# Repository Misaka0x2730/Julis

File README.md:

# Julis
Expansion test board of ARM Debugger for NUCLEO-F746ZG.

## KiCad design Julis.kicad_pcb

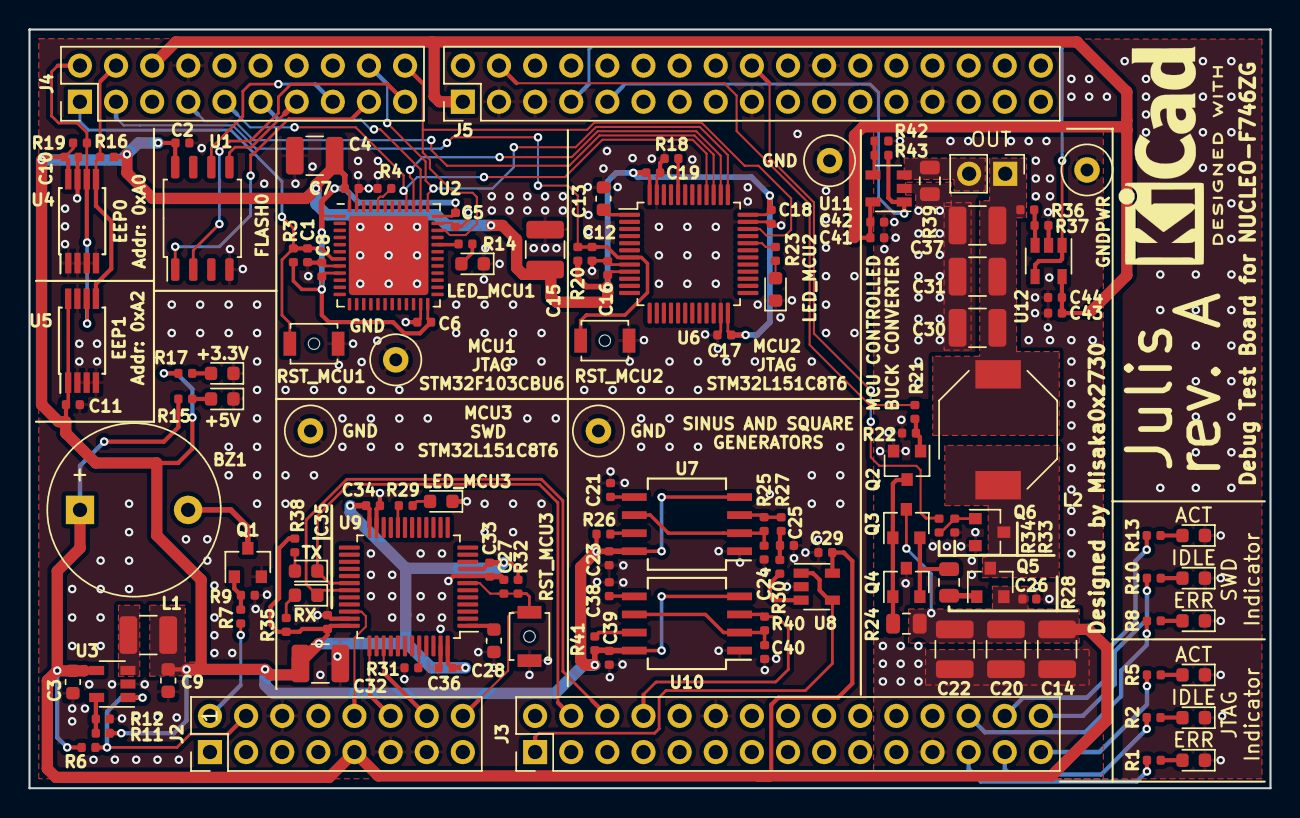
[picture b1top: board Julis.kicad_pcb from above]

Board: 2 copper layers, 87.2 x 53.3 mm, 134 parts (0 on the bottom side), 83 nets.

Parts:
BZ1: HCM1205X; Buzzer_12x9.5RM7.6
C1, C2, C5, C6, C7, C8, C10, C11, C12, C16, C17, C18, C19, C21, C23, C26, C27, C29, C33, C34, C35, C36, C38, C39, C41, C43: 0.1uF; C_0402_1005Metric
C3: 4.7uF; C_0603_1608Metric
C4, C14, C15, C20, C22, C30, C31, C32, C37: 22uF; C_1210_3225Metric
C9: 10uF; C_0603_1608Metric
C13, C28: 1uF; C_0603_1608Metric
C24, C25, C40: 68pF; C_0402_1005Metric
C42, C44: 10nF; C_0402_1005Metric
D1, D4: ERR; LED_0603_1608Metric
D2, D5: IDLE; LED_0603_1608Metric
D3, D6: ACT; LED_0603_1608Metric
D7: LED_MCU1; LED_0603_1608Metric
D8: +5V; LED_0603_1608Metric
D9: +3.3V; LED_0603_1608Metric
D10: LED_MCU2; LED_0603_1608Metric
D11: LED_MCU3; LED_0603_1608Metric
D12: RX; LED_0603_1608Metric
D13: TX; LED_0603_1608Metric
J1: OUT; PinHeader_1x02_P2.54mm_Vertical
J2: Conn_02x08_Odd_Even; PinHeader_2x08_P2.54mm_Vertical
J3: Conn_02x15_Odd_Even; PinHeader_2x15_P2.54mm_Vertical
J4: Conn_02x10_Odd_Even; PinHeader_2x10_P2.54mm_Vertical
J5: Conn_02x17_Odd_Even; PinHeader_2x17_P2.54mm_Vertical
L1: 2.2uH; L_1210_3225Metric
L2: 100uH; L_Bourns-SRU8043
Q1, Q2, Q6: IRLML2502; SOT-23
Q3: BC817; SOT-23
Q4: BC807; SOT-23
Q5: IRLML6402; SOT-23
R1, R2, R5, R8, R10, R13, R14, R15, R17, R23, R29, R35, R38: 510; R_0402_1005Metric
R3, R4, R18, R20, R31, R32: 10k; R_0402_1005Metric
R6, R9, R12, R22, R25, R26, R33, R36, R37, R40, R41: 100k; R_0402_1005Metric
R7, R21, R30, R34, R42: 1k; R_0402_1005Metric
R11: 453k; R_0402_1005Metric
R16, R19: 3.3k; R_0402_1005Metric
R24: 1k; R_0805_2012Metric
R27: 24k; R_0402_1005Metric
R28: 33; R_0805_2012Metric
R39: 0.1; R_0805_2012Metric
R43: 200k; R_0402_1005Metric
SW1: RST_MCU1; SW_SPST_B3U-1000P-B
SW2: RST_MCU2; SW_SPST_B3U-1000P-B
SW3: RST_MCU3; SW_SPST_B3U-1000P-B
TP1: GNDPWR; TestPoint_Loop_D3.50mm_Drill0.9mm_Beaded
TP2, TP3, TP4, TP5: GND; TestPoint_Loop_D3.50mm_Drill0.9mm_Beaded
U1: W25Q32JVSS; SOIC-8_5.23x5.23mm_P1.27mm
U2: STM32F103CBUx; QFN-48-1EP_7x7mm_P0.5mm_EP5.6x5.6mm
U3: TLV62568DBV; SOT-23-5
U4, U5: M24C02-WDW; TSSOP-8_4.4x3mm_P0.65mm
U6, U9: STM32L151C8TxA; LQFP-48_7x7mm_P0.5mm
U7, U10: LMC555xM; SO-8_5.3x6.2mm_P1.27mm
U8, U11, U12: TLV2371DBV; SOT-23-5

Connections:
+3V3: C2.2, C4.2, C5.2, C6.2, C7.2, C8.2, C9.1, C10.2, C11.2, C15.2, C16.2, C17.2, C18.2, C19.2, C23.2, C32.2, C33.2, C34.2, C35.2, C36.2, C39.2, L1.2, R3.1, R11.2, R16.1, R17.1, R19.1, R20.1, R26.2, R32.1, R35.1, R38.1, R41.2, U1.8, U2.1, U2.9, U2.24, U2.36, U2.48, U4.8, U5.1, U5.8, U6.9, U6.24, U6.36, U6.48, U7.4, U7.8, U9.9, U9.24, U9.36, U9.48, U10.4, U10.8
+5V: BZ1.1, C3.1, C14.2, C20.2, C22.2, C26.2, C29.2, J2.9, Q3.3, Q5.2, R6.2, R15.1, R24.1, U3.4, U8.5
/A0: J3.1, U8.1, U8.4
/A6: J5.7, U12.1, U12.4
/A7: J5.9, R43.2, U11.1
/AVDD: C41.2, C42.2, C43.2, C44.2, J4.6, J5.1, U11.5, U12.5
/D6: J5.4, R21.1
/D8: J4.20, U2.34, U6.34
/D9: J4.18, U2.37, U6.37
/D14: J4.4, R16.2, U4.5, U5.5
/D15: J4.2, R19.2, U4.6, U5.6
/D16: C1.1, J4.1, R3.2, SW1.2, U2.7
/D17: C12.1, J4.3, R20.2, SW2.2, U6.7
/D19: J4.7, U6.39
/D20: J4.9, U2.40, U6.40
/D21: J4.11, U2.38
/D22: J4.13, U1.5
/D23: J4.15, U1.6
/D24: J4.17, U1.1
/D25: J4.19, U1.2
/D42: J5.18, R34.2
/D43: J2.2, R7.1
/D44: J2.4, R6.1, U3.1
/D47: J2.10, U9.34
/D48: J2.12, U9.37
/D49: J2.14, U9.39
/D50: C27.1, J2.16, R32.2, SW3.2, U9.7
/D52: D13.1, J3.4, U9.30
/D53: D12.1, J3.6, U9.31
/D54: J3.8, R40.1, U10.3
/D62: J3.26, R8.1
/D63: J3.28, R13.1
/D64: J3.30, R10.1
/D65: J3.29, R5.1
/D66: J3.27, R2.1
/D67: J3.25, R1.1
/TDO_1: U2.39, U6.38
GND: C1.2, C2.1, C3.2, C4.1, C5.1, C6.1, C7.1, C8.1, C9.2, C10.1, C11.1, C12.2, C13.1, C15.1, C16.1, C17.1, C18.1, C19.1, C21.1, C23.1, C24.1, C25.1, C27.2, C28.1, C29.1, C32.1, C33.1, C34.1, C35.1, C36.1, C38.1, C39.1, C40.1, D1.1, D2.1, D3.1, D4.1, D5.1, D6.1, D7.1, D8.1, D9.1, D10.1, D11.1, J2.6, J2.11, J2.13, J3.12, J4.8, J5.3, J5.5, J5.17, J5.22, J5.27, Q1.2, R4.1, R9.2, R12.1, R18.1, R31.1, SW1.1, SW2.1, SW3.1, TP2.1, TP3.1, TP4.1, TP5.1, U1.4, U2.8, U2.23, U2.35, U2.47, U2.49, U3.2, U4.1, U4.2, U4.3, U4.4, U4.7, U5.2, U5.3, U5.4, U5.7, U6.8, U6.23, U6.35, U6.47, U7.1, U8.2, U9.8, U9.23, U9.35, U9.47, U10.1
GNDPWR: C14.1, C20.1, C22.1, C26.1, C30.1, C31.1, C37.1, C41.1, C42.1, C43.1, C44.1, J3.23, Q2.2, Q4.3, Q6.2, R22.2, R33.2, R37.1, R39.2, R42.2, TP1.1, U11.2, U12.2
unnamed: BZ1.2, Q1.3
unnamed: C13.2, U6.1
unnamed: C21.2, U7.5
unnamed: C24.2, R25.2, U7.2, U7.6
unnamed: C25.2, R27.2, R30.2
unnamed: C28.2, U9.1
unnamed: C30.2, C31.2, C37.2, J1.1, L2.2, R36.2
unnamed: C38.2, U10.5
unnamed: C40.2, R40.2, U10.2, U10.6
unnamed: D1.2, R1.2
unnamed: D2.2, R2.2
unnamed: D3.2, R5.2
unnamed: D4.2, R8.2
unnamed: D5.2, R10.2
unnamed: D6.2, R13.2
unnamed: D7.2, R14.2
unnamed: D8.2, R15.2
unnamed: D9.2, R17.2
unnamed: D10.2, R23.2
unnamed: D11.2, R29.2
unnamed: D12.2, R35.2
unnamed: D13.2, R38.2
unnamed: J1.2, R39.1, U11.3
unnamed: L1.1, U3.3
unnamed: L2.1, Q5.3, Q6.3
unnamed: Q1.1, R7.2, R9.1
unnamed: Q2.1, R21.2, R22.1
unnamed: Q2.3, Q3.1, Q4.1, R24.2
unnamed: Q3.2, Q4.2, R28.2
unnamed: Q5.1, R28.1
unnamed: Q6.1, R33.1, R34.1
unnamed: R4.2, U2.44
unnamed: R11.1, R12.2, U3.5
unnamed: R14.1, U2.32
unnamed: R18.2, U6.44
unnamed: R23.1, U6.32
unnamed: R25.1, R27.1, U7.3
unnamed: R26.1, U7.7
unnamed: R29.1, U9.20
unnamed: R30.1, U8.3
unnamed: R31.2, U9.44
unnamed: R36.1, R37.2, U12.3
unnamed: R41.1, U10.7
unnamed: R42.1, R43.1, U11.4

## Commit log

2019-09-22 Completed first board version.
2019-09-22 Update README
    Fixed description.
2019-09-23 Missing values has been calculated.
2019-09-24 Fixed some footprints and values.
2019-09-24 Fixed pcb silkscreen.
2019-09-29 Add Gerber files.
